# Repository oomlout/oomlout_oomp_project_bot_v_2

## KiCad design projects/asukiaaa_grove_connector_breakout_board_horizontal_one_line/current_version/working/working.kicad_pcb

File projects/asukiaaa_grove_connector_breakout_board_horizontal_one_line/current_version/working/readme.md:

# grove_connector_breakout_board
 
## summary 
* id: asukiaaa_grove_connector_breakout_board_horizontal_one_line
* user: asukiaaa
* name: grove_connector_breakout_board
* board: horizontal_one_line
* repo: https://github.com/asukiaaa/grove-connector-breakout-board
* src_file_repo_kicad_pcb: horizontal-one-line/horizontal-one-line.kicad_pcb
* src_file_repo_kicad_pcb_link: https://github.com/asukiaaa/grove-connector-breakout-board/tree/master/horizontal-one-line/horizontal-one-line.kicad_pcb
* src_file_repo_kicad_sch: horizontal-one-line/horizontal-one-line.kicad_sch
* src_file_repo_kicad_sch_link: https://github.com/asukiaaa/grove-connector-breakout-board/tree/master/horizontal-one-line/horizontal-one-line.kicad_sch

* src_file_repo_sch: 
* src_file_repo_sch_link: https://github.com/asukiaaa/grove-connector-breakout-board/tree/master/
* full details link: https://github.com/oomlout/oomlout_oomp_project_bot_v_2/tree/main/projects/asukiaaa_grove_connector_breakout_board_horizontal_one_line/current_version/working  

## schematic  
  
[schematic (pdf)](working_schematic.pdf) 

## pcb  

[board (pdf)](working.pdf)  

## working_bom
| Id | Designator | Footprint | Quantity | Designation | Supplier and ref |  | None | 
| --- | --- | --- | --- | --- | --- | --- | --- | 
| 1 | J1 | NS-Tech_Grove_1x04_P2mm_Horizontal_silk_inside | 1 | Grove-I2C-connector |  |  | [''] | 
| 2 | fid1,fid1 | Fiducial_0.5mm_Mask1mm | 2 | Fiducial_0.5mm_Mask1mm |  |  | [''] | 
| 3 | J2 | PinHeader_1x04_P2.54mm_Vertical_silk_inside | 1 | Conn_01x04 |  |  | [''] | 

## bom_schematic
| Ref | Qnty | Value | Cmp name | Footprint | Description | Vendor | DNP | 
| --- | --- | --- | --- | --- | --- | --- | --- | 
| J1 | 1 | Grove-I2C-connector | Grove-I2C-connector | my-kicad-footprints:NS-Tech_Grove_1x04_P2mm_Horizontalnside_silk_i |  |  |  | 
| J2 | 1 | Conn_01x04 | Conn_01x04 | my-kicad-footprints:PinHeader_1x04_P2.54mm_Vertical_silk_inside | Generic connector, single row, 01x04, script generated (kicad-library-utils/schlib/autogen/connector/) |  |  |

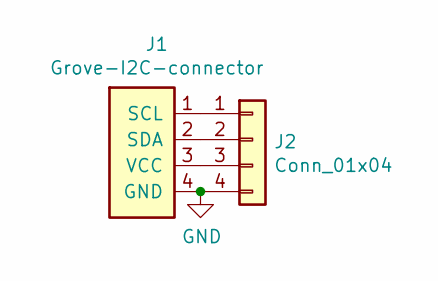
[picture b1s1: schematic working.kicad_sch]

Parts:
J1: Grove-I2C-connector; NS-Tech_Grove_1x04_P2mm_Horizontalnside_silk_i
J2: Conn_01x04; PinHeader_1x04_P2.54mm_Vertical_silk_inside

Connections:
GND: J1.4 (GND), J2.4
unnamed: J1.1 (SCL), J2.1
unnamed: J1.2 (SDA), J2.2
unnamed: J1.3 (VCC), J2.3

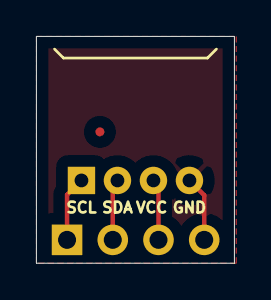
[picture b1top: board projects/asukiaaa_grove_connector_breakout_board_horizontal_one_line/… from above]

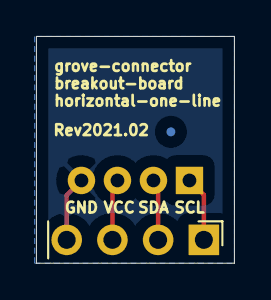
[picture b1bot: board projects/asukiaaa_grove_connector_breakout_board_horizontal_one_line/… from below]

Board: 2 copper layers, 11.0 x 12.6 mm, 4 parts (2 on the bottom side), 4 nets.

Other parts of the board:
fid1, fid1#2: Fiducial_0.5mm_Mask1mm

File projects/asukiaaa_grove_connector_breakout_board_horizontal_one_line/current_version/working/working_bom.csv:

"Id";"Designator";"Footprint";"Quantity";"Designation";"Supplier and ref";
1;"J1";"NS-Tech_Grove_1x04_P2mm_Horizontal_silk_inside";1;"Grove-I2C-connector";;;
2;"fid1,fid1";"Fiducial_0.5mm_Mask1mm";2;"Fiducial_0.5mm_Mask1mm";;;
3;"J2";"PinHeader_1x04_P2.54mm_Vertical_silk_inside";1;"Conn_01x04";;;

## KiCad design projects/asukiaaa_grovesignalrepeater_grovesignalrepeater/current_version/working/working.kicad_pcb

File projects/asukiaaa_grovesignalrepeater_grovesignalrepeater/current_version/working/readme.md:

# grovesignalrepeater
 
## summary 
* id: asukiaaa_grovesignalrepeater_grovesignalrepeater
* user: asukiaaa
* name: grovesignalrepeater
* board: grovesignalrepeater
* repo: https://github.com/asukiaaa/GroveSignalRepeater
* src_file_repo_kicad_pcb: GroveSignalRepeater.kicad_pcb
* src_file_repo_kicad_pcb_link: https://github.com/asukiaaa/GroveSignalRepeater/tree/master/GroveSignalRepeater.kicad_pcb

* src_file_repo_sch: GroveSignalRepeater.sch
* src_file_repo_sch_link: https://github.com/asukiaaa/GroveSignalRepeater/tree/master/GroveSignalRepeater.sch
* full details link: https://github.com/oomlout/oomlout_oomp_project_bot_v_2/tree/main/projects/asukiaaa_grovesignalrepeater_grovesignalrepeater/current_version/working  

## schematic  
  
[schematic (pdf)](working_schematic.pdf) 

## pcb  

[board (pdf)](working.pdf)  

## working_bom
| Id | Designator | Footprint | Quantity | Designation | Supplier and ref |  | None | 
| --- | --- | --- | --- | --- | --- | --- | --- | 
| 1 | J1,J2 | NS-Tech_Grove_1x04_P2mm_Horizontal | 2 | Conn_01x04 |  |  | [''] | 
| 2 | Q1,Q2,Q3,Q4 | SOT-23 | 4 | Q_NMOS_GSD |  |  | [''] | 
| 3 | R1,R2,R3,R4,R5,R6 | R_0603_1608Metric | 6 | 10k |  |  | [''] | 

## bom_schematic
| Ref | Qnty | Value | Cmp name | Footprint | Description | Vendor | DNP | 
| --- | --- | --- | --- | --- | --- | --- | --- | 
| J1, J2 | 2 | Conn_01x04 | Conn_01x04 | my-kicad-footprints:NS-Tech_Grove_1x04_P2mm_Horizontal | Generic connector, single row, 01x04, script generated (kicad-library-utils/schlib/autogen/connector/) |  |  | 
| Q1, Q2, Q3, Q4 | 4 | Q_NMOS_GSD | Q_NMOS_GSD | Package_TO_SOT_SMD:SOT-23 | N-MOSFET transistor, gate/source/drain |  |  | 
| R1, R2, R3, R4, R5, R6 | 6 | 10k | R | Resistor_SMD:R_0603_1608Metric | Resistor |  |  |

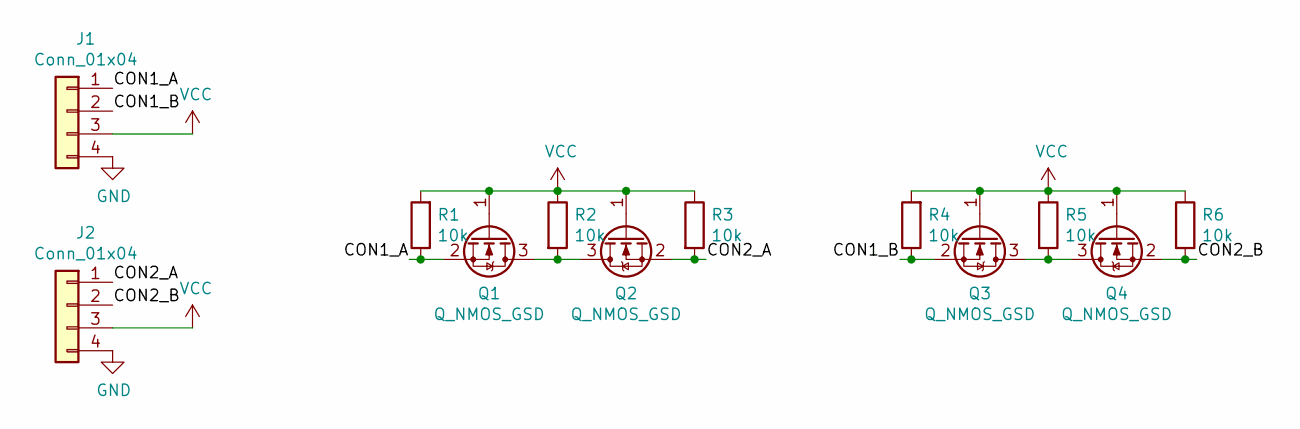
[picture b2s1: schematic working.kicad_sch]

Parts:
J1, J2: Conn_01x04; NS-Tech_Grove_1x04_P2mm_Horizontal
Q1, Q2, Q3, Q4: Q_NMOS_GSD; SOT-23
R1, R2, R3, R4, R5, R6: 10k; R_0603_1608Metric

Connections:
/CON1_A: J1.1, Q1.2 (S), R1.1
/CON1_B: J1.2, Q3.2 (S), R4.1
/CON2_A: J2.1, Q2.2 (S), R3.2
/CON2_B: J2.2, Q4.2 (S), R6.2
GND: J1.4, J2.4
unnamed: Q1.3 (D), Q2.3 (D), R2.2
unnamed: Q3.3 (D), Q4.3 (D), R5.2
VCC: J1.3, J2.3, Q1.1 (G), Q2.1 (G), Q3.1 (G), Q4.1 (G), R1.2, R2.1, R3.1, R4.2, R5.1, R6.1

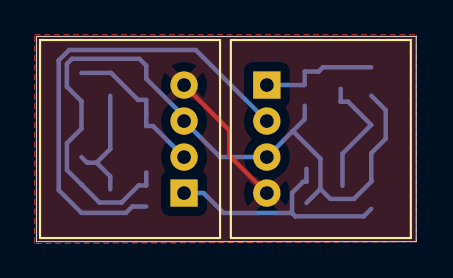
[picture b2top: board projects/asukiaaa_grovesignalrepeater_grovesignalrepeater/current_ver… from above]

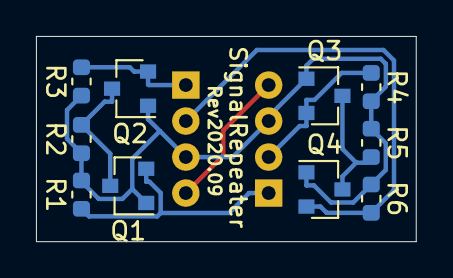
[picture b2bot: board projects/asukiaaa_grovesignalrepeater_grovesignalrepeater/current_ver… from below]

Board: 2 copper layers, 21.1 x 11.4 mm, 12 parts (10 on the bottom side), 8 nets.

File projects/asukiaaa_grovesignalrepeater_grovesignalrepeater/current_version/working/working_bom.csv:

"Id";"Designator";"Footprint";"Quantity";"Designation";"Supplier and ref";
1;"J1,J2";"NS-Tech_Grove_1x04_P2mm_Horizontal";2;"Conn_01x04";;;
2;"Q1,Q2,Q3,Q4";"SOT-23";4;"Q_NMOS_GSD";;;
3;"R1,R2,R3,R4,R5,R6";"R_0603_1608Metric";6;"10k";;;

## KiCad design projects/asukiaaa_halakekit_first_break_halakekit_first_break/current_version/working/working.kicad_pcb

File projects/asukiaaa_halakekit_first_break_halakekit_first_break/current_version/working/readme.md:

# halakekit_first_break
 
## summary 
* id: asukiaaa_halakekit_first_break_halakekit_first_break
* user: asukiaaa
* name: halakekit_first_break
* board: halakekit_first_break
* repo: https://github.com/asukiaaa/halakekit_first_break
* src_file_repo_kicad_pcb: halakekit_first_break.kicad_pcb
* src_file_repo_kicad_pcb_link: https://github.com/asukiaaa/halakekit_first_break/tree/master/halakekit_first_break.kicad_pcb

* src_file_repo_sch: halakekit_first_break.sch
* src_file_repo_sch_link: https://github.com/asukiaaa/halakekit_first_break/tree/master/halakekit_first_break.sch
* full details link: https://github.com/oomlout/oomlout_oomp_project_bot_v_2/tree/main/projects/asukiaaa_halakekit_first_break_halakekit_first_break/current_version/working  

## schematic  
  
[schematic (pdf)](working_schematic.pdf) 

## pcb  

[board (pdf)](working.pdf)  

## working_bom
| Id | Designator | Footprint | Quantity | Designation | Supplier and ref |  | None | 
| --- | --- | --- | --- | --- | --- | --- | --- | 
| 1 | J21,J22 | Pin_Header_Straight_1x10 | 2 | LINE_10 |  |  | [''] | 
| 2 | J26 | Pin_Header_Straight_1x02 | 1 | HEADER_2 |  |  | [''] | 
| 3 | J27 | Pin_Header_Straight_1x12 | 1 | HEADER_12 |  |  | [''] | 
| 4 | U1 | Arduino Pro Micro | 1 | Arduino_Pro_Micro |  |  | [''] | 
| 5 | G***,G***,G*** | nyampass_logo_8p4mm | 3 | LOGO |  |  | [''] | 
| 6 | J1,J2,J3,J4,J5,J11,J12,J13,J14,J15 | Pin_Header_Connect_1x04 | 10 | LINE_4 |  |  | [''] | 
| 7 | J6 | Pin_Header_Straight_1x10 | 1 | HEADER_10 |  |  | [''] | 
| 8 | J9,J10,J7,J8 | Pin_Header_Straight_1x04 | 4 | Connector_4 |  |  | [''] | 
| 9 | J24,J28 | Pin_Header_Circle_1x04 | 2 | CIRCLES_4 |  |  | [''] | 

## bom_schematic
| Ref | Qnty | Value | Cmp name | Footprint | Description | Vendor | DNP | 
| --- | --- | --- | --- | --- | --- | --- | --- | 
| J1, J2, J3, J4, J5, J11, J12, J13, J14, J15 | 10 | LINE_4 | HEADER_4 | simple_headers:Pin_Header_Connect_1x04 |  |  |  | 
| J6 | 1 | HEADER_10 | HEADER_10 | simple_headers:Pin_Header_Straight_1x10 |  |  |  | 
| J7, J8, J9, J10 | 4 | Connector_4 | HEADER_4 | simple_headers:Pin_Header_Straight_1x04 |  |  |  | 
| J21, J22 | 2 | LINE_10 | HEADER_10 | simple_headers:Pin_Header_Straight_1x10 |  |  |  | 
| J24, J28 | 2 | CIRCLES_4 | HEADER_4 | simple_headers:Pin_Header_Circle_1x04 |  |  |  | 
| J26 | 1 | HEADER_2 | HEADER_2 | simple_headers:Pin_Header_Straight_1x02 |  |  |  | 
| J27 | 1 | HEADER_12 | HEADER_12 | simple_headers:Pin_Header_Straight_1x12 |  |  |  | 
| U1 | 1 | Arduino_Pro_Micro | Arduino_Pro_Micro | arduino_pro_micro:Arduino Pro Micro |  |  |  |

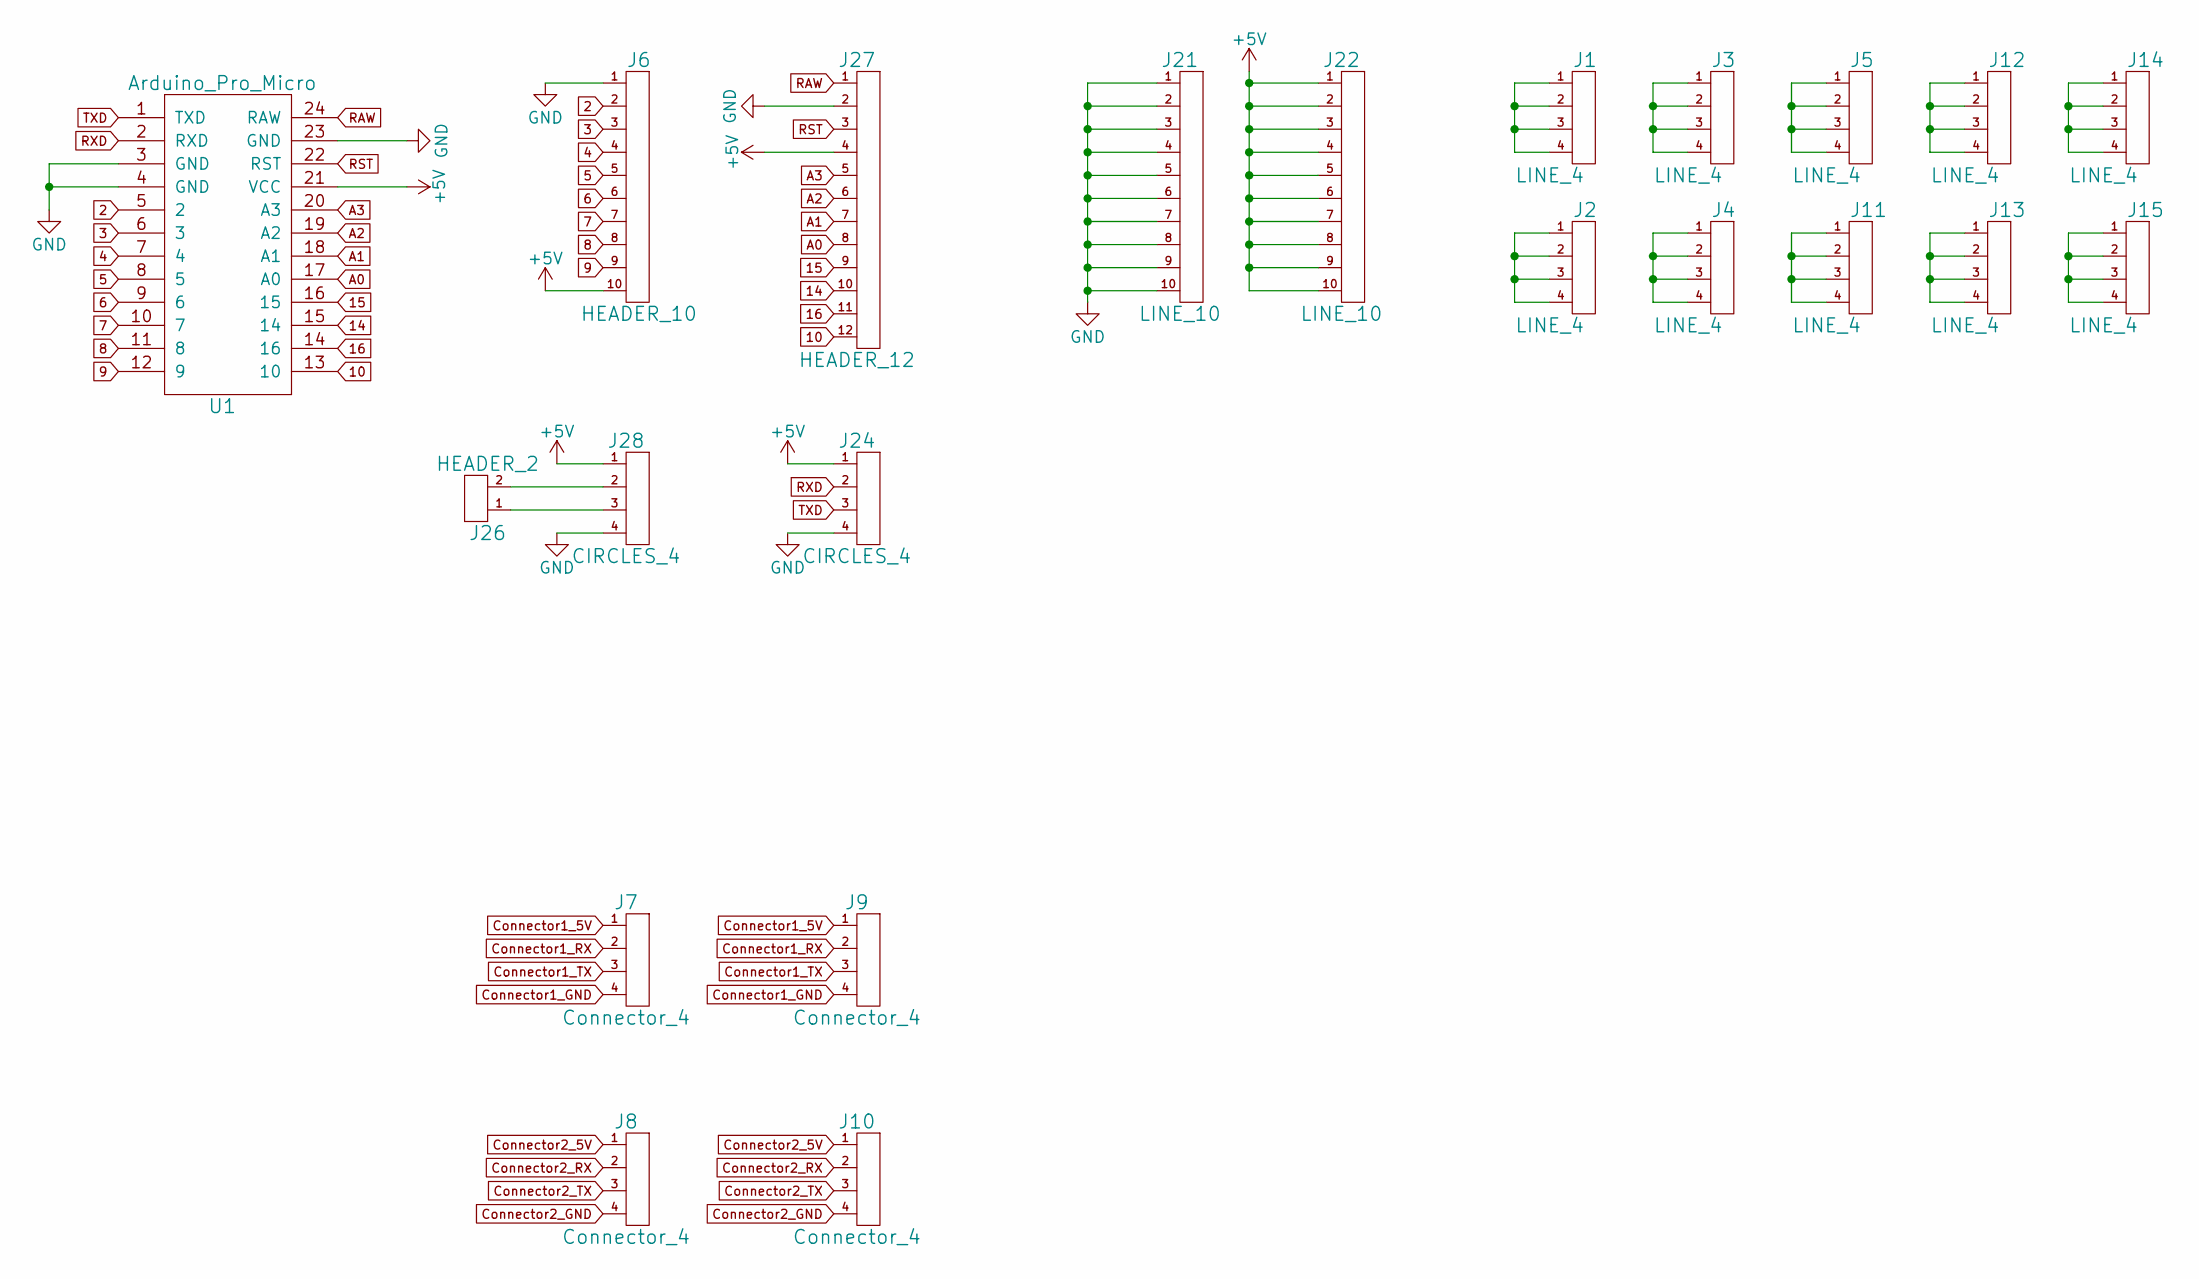
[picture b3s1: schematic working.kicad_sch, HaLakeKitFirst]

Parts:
J1, J2, J3, J4, J5, J11, J12, J13, J14, J15: LINE_4; Pin_Header_Connect_1x04
J6: HEADER_10; Pin_Header_Straight_1x10
J7, J8, J9, J10: Connector_4; Pin_Header_Straight_1x04
J21, J22: LINE_10; Pin_Header_Straight_1x10
J24, J28: CIRCLES_4; Pin_Header_Circle_1x04
J26: HEADER_2; Pin_Header_Straight_1x02
J27: HEADER_12; Pin_Header_Straight_1x12
U1: Arduino_Pro_Micro; Arduino Pro Micro

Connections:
2: J6.2, U1.5 (2)
3: J6.3, U1.6 (3)
4: J6.4, U1.7 (4)
5: J6.5, U1.8 (5)
6: J6.6, U1.9 (6)
7: J6.7, U1.10 (7)
8: J6.8, U1.11 (8)
9: J6.9, U1.12 (9)
10: J27.12, U1.13 (10)
14: J27.10, U1.15 (14)
15: J27.9, U1.16 (15)
16: J27.11, U1.14 (16)
+5V: J6.10, J22.1, J22.2, J22.3, J22.4, J22.5, J22.6, J22.7, J22.8, J22.9, J22.10, J24.1, J27.4, J28.1, U1.21 (VCC)
A0: J27.8, U1.17 (A0)
A1: J27.7, U1.18 (A1)
A2: J27.6, U1.19 (A2)
A3: J27.5, U1.20 (A3)
Connector1_5V: J7.1, J9.1
Connector1_GND: J7.4, J9.4
Connector1_RX: J7.2, J9.2
Connector1_TX: J7.3, J9.3
Connector2_5V: J8.1, J10.1
Connector2_GND: J8.4, J10.4
Connector2_RX: J8.2, J10.2
Connector2_TX: J8.3, J10.3
GND: J6.1, J21.1, J21.2, J21.3, J21.4, J21.5, J21.6, J21.7, J21.8, J21.9, J21.10, J24.4, J27.2, J28.4, U1.3 (GND), U1.4 (GND), U1.23 (GND)
unnamed: J1.1, J1.2, J1.3, J1.4
unnamed: J2.1, J2.2, J2.3, J2.4
unnamed: J3.1, J3.2, J3.3, J3.4
unnamed: J4.1, J4.2, J4.3, J4.4
unnamed: J5.1, J5.2, J5.3, J5.4
unnamed: J11.1, J11.2, J11.3, J11.4
unnamed: J12.1, J12.2, J12.3, J12.4
unnamed: J13.1, J13.2, J13.3, J13.4
unnamed: J14.1, J14.2, J14.3, J14.4
unnamed: J15.1, J15.2, J15.3, J15.4
unnamed: J26.1, J28.3
unnamed: J26.2, J28.2
RAW: J27.1, U1.24 (RAW)
RST: J27.3, U1.22 (RST)
RXD: J24.2, U1.2 (RXD)
TXD: J24.3, U1.1 (TXD)

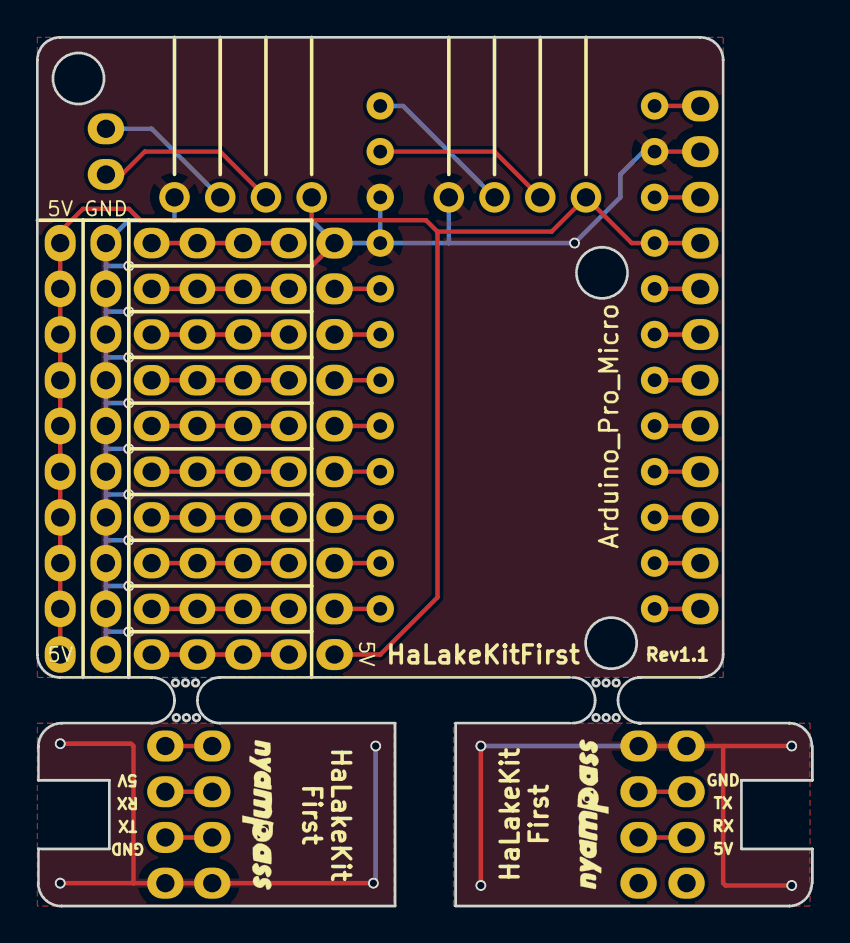
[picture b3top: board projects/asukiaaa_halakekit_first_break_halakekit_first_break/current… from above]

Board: 2 copper layers, 43.1 x 48.3 mm, 22 parts (0 on the bottom side), 42 nets.

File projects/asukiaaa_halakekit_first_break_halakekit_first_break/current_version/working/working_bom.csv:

"Id";"Designator";"Footprint";"Quantity";"Designation";"Supplier and ref";
1;"J21,J22";"Pin_Header_Straight_1x10";2;"LINE_10";;;
2;"J26";"Pin_Header_Straight_1x02";1;"HEADER_2";;;
3;"J27";"Pin_Header_Straight_1x12";1;"HEADER_12";;;
4;"U1";"Arduino Pro Micro";1;"Arduino_Pro_Micro";;;
5;"G***,G***,G***";"nyampass_logo_8p4mm";3;"LOGO";;;
6;"J1,J2,J3,J4,J5,J11,J12,J13,J14,J15";"Pin_Header_Connect_1x04";10;"LINE_4";;;
7;"J6";"Pin_Header_Straight_1x10";1;"HEADER_10";;;
8;"J9,J10,J7,J8";"Pin_Header_Straight_1x04";4;"Connector_4";;;
9;"J24,J28";"Pin_Header_Circle_1x04";2;"CIRCLES_4";;;

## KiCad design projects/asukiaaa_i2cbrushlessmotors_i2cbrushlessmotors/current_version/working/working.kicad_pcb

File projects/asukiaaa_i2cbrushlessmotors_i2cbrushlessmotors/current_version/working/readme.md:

# i2cbrushlessmotors
 
## summary 
* id: asukiaaa_i2cbrushlessmotors_i2cbrushlessmotors
* user: asukiaaa
* name: i2cbrushlessmotors
* board: i2cbrushlessmotors
* repo: https://github.com/asukiaaa/I2cBrushlessMotors
* src_file_repo_kicad_pcb: pcb/I2cBrushlessMotors.kicad_pcb
* src_file_repo_kicad_pcb_link: https://github.com/asukiaaa/I2cBrushlessMotors/tree/master/pcb/I2cBrushlessMotors.kicad_pcb

* src_file_repo_sch: pcb/I2cBrushlessMotors.sch
* src_file_repo_sch_link: https://github.com/asukiaaa/I2cBrushlessMotors/tree/master/pcb/I2cBrushlessMotors.sch
* full details link: https://github.com/oomlout/oomlout_oomp_project_bot_v_2/tree/main/projects/asukiaaa_i2cbrushlessmotors_i2cbrushlessmotors/current_version/working  

## schematic  
  
[schematic (pdf)](working_schematic.pdf) 

## pcb  

[board (pdf)](working.pdf)  

## working_bom
| Id | Designator | Footprint | Quantity | Designation | Supplier and ref |  | None | 
| --- | --- | --- | --- | --- | --- | --- | --- | 
| 1 | J3 | PinHeader_2x15_P2.54mm_M5Stack | 1 | Header |  |  | [''] | 
| 2 | J4 | PinSocket_2x15_P2.54mm_Vertical_SMD_just_for_M5Stack_bottom | 1 | Socket |  |  | [''] | 
| 3 | C1,C3 | C_0603_1608Metric | 2 | 0.1uf |  |  | [''] | 
| 4 | J2 | 2x03_P2.54mm_Pads | 1 | Conn_01x06 |  |  | [''] | 
| 5 | R3,R2,R1,R5,R8,R4,R7,R6,R9,R11,R14,R17,R10,R13,R16,R12,R15,R18 | R_0603_1608Metric | 18 | 10k |  |  | [''] | 
| 6 | J1,J5 | Molex_1x03_P1.25mm_Vertical | 2 | Conn_01x03 |  |  | [''] | 
| 7 | Q1,Q4,Q7,Q10,Q13,Q16 | SOT-23 | 6 | Q_PMOS_GSD |  |  | [''] | 
| 8 | Q2,Q3,Q5,Q8,Q6,Q9,Q11,Q14,Q17,Q12,Q15,Q18 | SOT-23 | 12 | Q_NMOS_GSD |  |  | [''] | 
| 9 | U1 | QFN-32-1EP_5x5mm_P0.5mm_EP3.1x3.1mm | 1 | ATmega328PB-MU |  |  | [''] | 
| 10 | C2 | C_0603_1608Metric | 1 | 1uf |  |  | [''] | 
| 11 | D1,D2 | D_SOD-323 | 2 | D |  |  | [''] | 
| 12 | D3 | D_SOD-123F | 1 | D |  |  | [''] | 

## bom_schematic
| Ref | Qnty | Value | Cmp name | Footprint | Description | Vendor | DNP | 
| --- | --- | --- | --- | --- | --- | --- | --- | 
| A0, A1, A4, A6 | 4 | NC | Jumper_NC_Small-Device | Jumper:SolderJumper-2_P1.3mm_Bridged_RoundedPad1.0x1.5mm |  |  |  | 
| A2, A3, A5, A7 | 4 | NO | Jumper_NO_Small-Device | Jumper:SolderJumper-2_P1.3mm_Open_RoundedPad1.0x1.5mm |  |  |  | 
| C1, C3 | 2 | 0.1uf | C | Capacitor_SMD:C_0603_1608Metric | Unpolarized capacitor |  |  | 
| C2 | 1 | 1uf | C | Capacitor_SMD:C_0603_1608Metric | Unpolarized capacitor |  |  | 
| D1, D2 | 2 | D | D | Diode_SMD:D_SOD-323 | Diode |  |  | 
| D3 | 1 | D | D | Diode_SMD:D_SOD-123F | Diode |  |  | 
| J1, J5 | 2 | Conn_01x03 | Conn_01x03 | footprints:Molex_1x03_P1.25mm_Vertical | Generic connector, single row, 01x03, script generated (kicad-library-utils/schlib/autogen/connector/) |  |  | 
| J2 | 1 | Conn_01x06 | Conn_01x06 | footprints:2x03_P2.54mm_Pads | Generic connector, single row, 01x06, script generated (kicad-library-utils/schlib/autogen/connector/) |  |  | 
| J3 | 1 | Header | Conn_02x15_Odd_Even | footprints:PinHeader_2x15_P2.54mm_M5Stack | Generic connector, double row, 02x15, odd/even pin numbering scheme (row 1 odd numbers, row 2 even numbers), script generated (kicad-library-utils/schlib/autogen/connector/) |  |  | 
| J4 | 1 | Socket | Conn_02x15_Odd_Even | footprints:PinSocket_2x15_P2.54mm_Vertical_SMD_just_for_M5Stack_bottom | Generic connector, double row, 02x15, odd/even pin numbering scheme (row 1 odd numbers, row 2 even numbers), script generated (kicad-library-utils/schlib/autogen/connector/) |  |  | 
| Q1, Q4, Q7, Q10, Q13, Q16 | 6 | Q_PMOS_GSD | Q_PMOS_GSD | Package_TO_SOT_SMD:SOT-23 | P-MOSFET transistor, gate/source/drain |  |  | 
| Q2, Q3, Q5, Q6, Q8, Q9, Q11, Q12, Q14, Q15, Q17, Q18 | 12 | Q_NMOS_GSD | Q_NMOS_GSD | Package_TO_SOT_SMD:SOT-23 | N-MOSFET transistor, gate/source/drain |  |  | 
| R1, R2, R3, R4, R5, R6, R7, R8, R9, R10, R11, R12, R13, R14, R15, R16, R17, R18 | 18 | 10k | R | Resistor_SMD:R_0603_1608Metric | Resistor |  |  | 
| U1 | 1 | ATmega328PB-MU | ATmega328PB-MU-MCU_Microchip_ATmega | Package_DFN_QFN:QFN-32-1EP_5x5mm_P0.5mm_EP3.1x3.1mm |  |  |  |

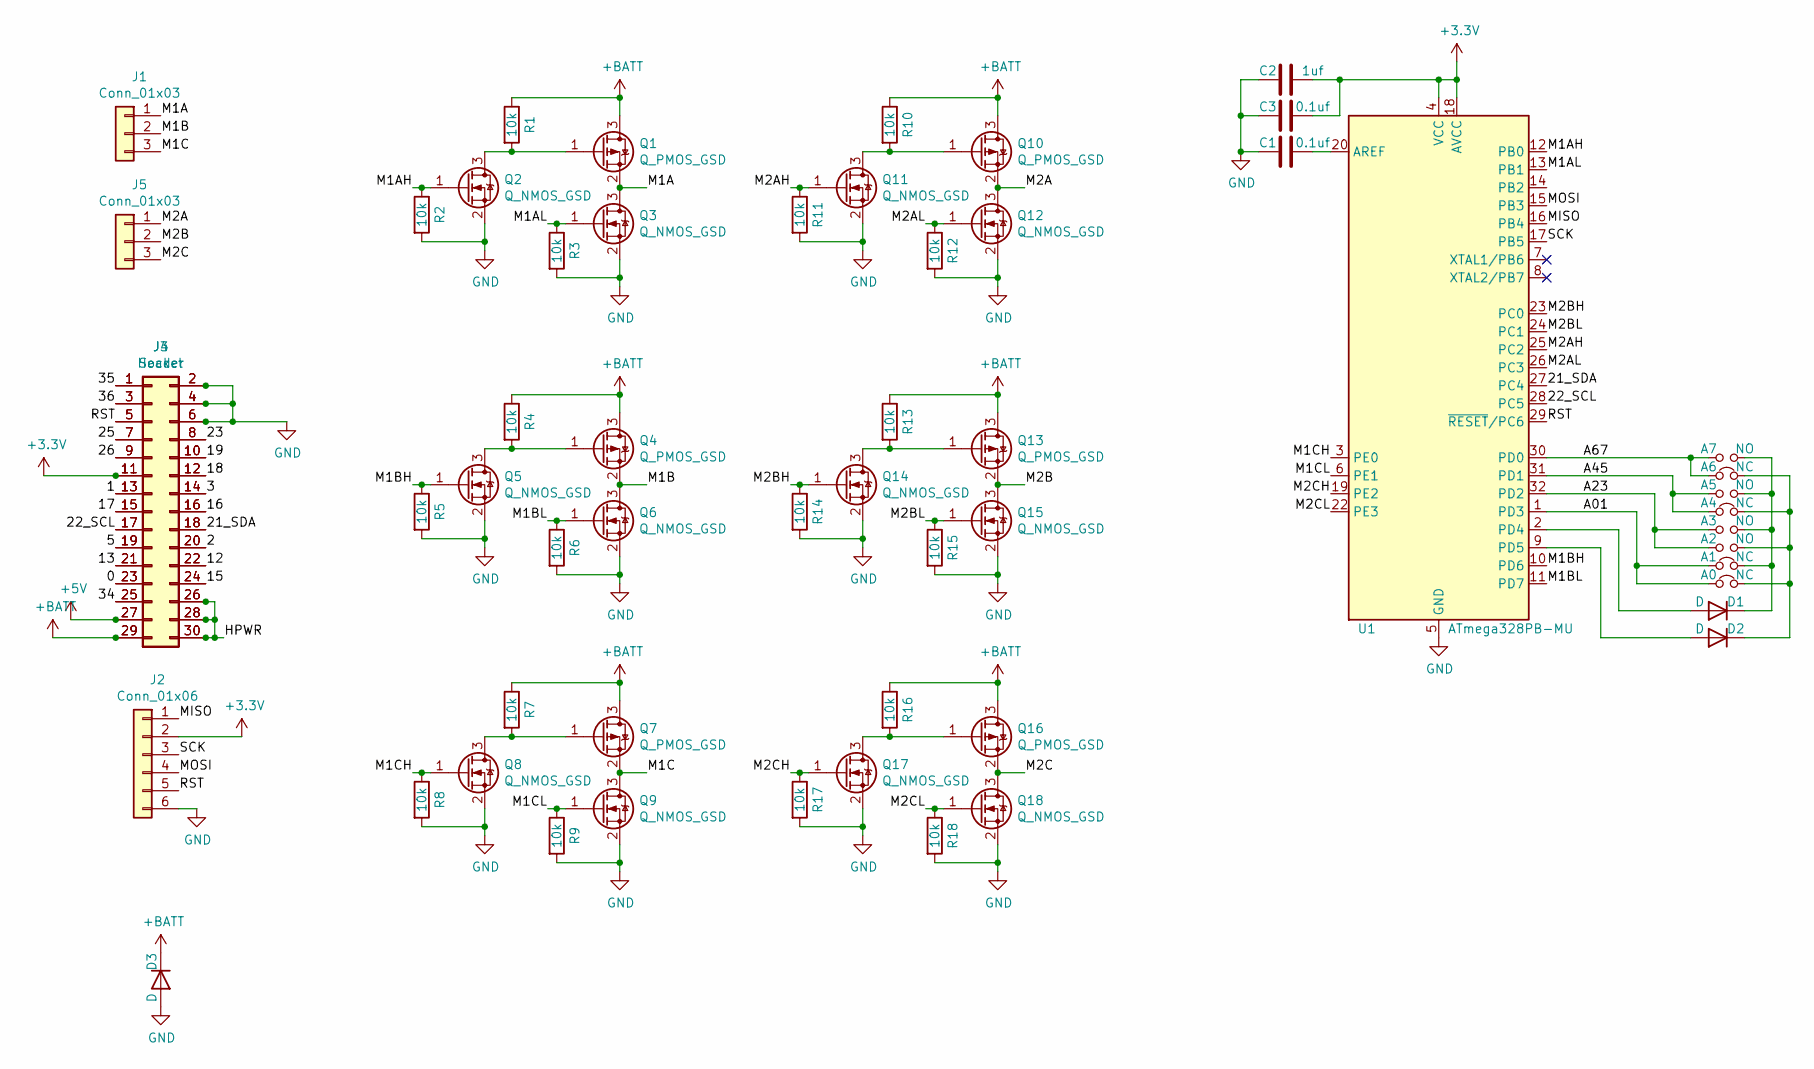
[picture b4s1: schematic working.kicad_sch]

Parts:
A0, A1, A4, A6: NC; SolderJumper-2_P1.3mm_Bridged_RoundedPad1.0x1.5mm
A2, A3, A5, A7: NO; SolderJumper-2_P1.3mm_Open_RoundedPad1.0x1.5mm
C1, C3: 0.1uf; C_0603_1608Metric
C2: 1uf; C_0603_1608Metric
D1, D2: D; D_SOD-323
D3: D; D_SOD-123F
J1, J5: Conn_01x03; Molex_1x03_P1.25mm_Vertical
J2: Conn_01x06; 2x03_P2.54mm_Pads
J3: Header; PinHeader_2x15_P2.54mm_M5Stack
J4: Socket; PinSocket_2x15_P2.54mm_Vertical_SMD_just_for_M5Stack_bottom
Q1, Q4, Q7, Q10, Q13, Q16: Q_PMOS_GSD; SOT-23
Q2, Q3, Q5, Q6, Q8, Q9, Q11, Q12, Q14, Q15, Q17, Q18: Q_NMOS_GSD; SOT-23
R1, R2, R3, R4, R5, R6, R7, R8, R9, R10, R11, R12, R13, R14, R15, R16, R17, R18: 10k; R_0603_1608Metric
U1: ATmega328PB-MU; QFN-32-1EP_5x5mm_P0.5mm_EP3.1x3.1mm

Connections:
+3V3: C2.2, C3.2, J2.2, J3.11, J4.11, U1.4 (VCC), U1.18 (AVCC)
+5V: J3.27, J4.27
+BATT: D3.1 (K), J3.29, J4.29, Q1.3 (D), Q4.3 (D), Q7.3 (D), Q10.3 (D), Q13.3 (D), Q16.3 (D), R1.1, R4.1, R7.1, R10.1, R13.1, R16.1
/0: J3.23, J4.23
/1: J3.13, J4.13
/2: J3.20, J4.20
/3: J3.14, J4.14
/5: J3.19, J4.19
/12: J3.22, J4.22
/13: J3.21, J4.21
/15: J3.24, J4.24
/16: J3.16, J4.16
/17: J3.15, J4.15
/18: J3.12, J4.12
/19: J3.10, J4.10
/21_SDA: J3.18, J4.18, U1.27 (PC4)
/22_SCL: J3.17, J4.17, U1.28 (PC5)
/23: J3.8, J4.8
/25: J3.7, J4.7
/26: J3.9, J4.9
/34: J3.25, J4.25
/35: J3.1, J4.1
/36: J3.3, J4.3
/A01: A0.1, A1.1, U1.1 (PD3)
/A23: A2.1, A3.1, U1.32 (PD2)
/A45: A4.1, A5.1, U1.31 (PD1)
/A67: A6.1, A7.1, U1.30 (PD0)
/HPWR: J3.26, J3.28, J3.30, J4.26, J4.28, J4.30
/M1A: J1.1, Q1.2 (S), Q3.3 (D)
/M1AH: Q2.1 (G), R2.1, U1.12 (PB0)
/M1AL: Q3.1 (G), R3.1, U1.13 (PB1)
/M1B: J1.2, Q4.2 (S), Q6.3 (D)
/M1BH: Q5.1 (G), R5.1, U1.10 (PD6)
/M1BL: Q6.1 (G), R6.1, U1.11 (PD7)
/M1C: J1.3, Q7.2 (S), Q9.3 (D)
/M1CH: Q8.1 (G), R8.1, U1.3 (PE0)
/M1CL: Q9.1 (G), R9.1, U1.6 (PE1)
/M2A: J5.1, Q10.2 (S), Q12.3 (D)
/M2AH: Q11.1 (G), R11.1, U1.25 (PC2)
/M2AL: Q12.1 (G), R12.1, U1.26 (PC3)
/M2B: J5.2, Q13.2 (S), Q15.3 (D)
/M2BH: Q14.1 (G), R14.1, U1.23 (PC0)
/M2BL: Q15.1 (G), R15.1, U1.24 (PC1)
/M2C: J5.3, Q16.2 (S), Q18.3 (D)
/M2CH: Q17.1 (G), R17.1, U1.19 (PE2)
/M2CL: Q18.1 (G), R18.1, U1.22 (PE3)
/MISO: J2.1, U1.16 (PB4)
/MOSI: J2.4, U1.15 (PB3)
/RST: J2.5, J3.5, J4.5, U1.29 (~RESET/PC6)
/SCK: J2.3, U1.17 (PB5)
GND: C1.1, C2.1, C3.1, D3.2 (A), J2.6, J3.2, J3.4, J3.6, J4.2, J4.4, J4.6, Q2.2 (S), Q3.2 (S), Q5.2 (S), Q6.2 (S), Q8.2 (S), Q9.2 (S), Q11.2 (S), Q12.2 (S), Q14.2 (S), Q15.2 (S), Q17.2 (S), Q18.2 (S), R2.2, R3.2, R5.2, R6.2, R8.2, R9.2, R11.2, R12.2, R14.2, R15.2, R17.2, R18.2, U1.5 (GND), U1.21 (GND), U1.33 (GND)
unnamed: A0.2, A2.2, A4.2, A6.2, D2.1 (K)
unnamed: A1.2, A3.2, A5.2, A7.2, D1.1 (K)
unnamed: C1.2, U1.20 (AREF)
unnamed: D1.2 (A), U1.2 (PD4)
unnamed: D2.2 (A), U1.9 (PD5)
unnamed: Q1.1 (G), Q2.3 (D), R1.2
unnamed: Q4.1 (G), Q5.3 (D), R4.2
unnamed: Q7.1 (G), Q8.3 (D), R7.2
unnamed: Q10.1 (G), Q11.3 (D), R10.2
unnamed: Q13.1 (G), Q14.3 (D), R13.2
unnamed: Q16.1 (G), Q17.3 (D), R16.2

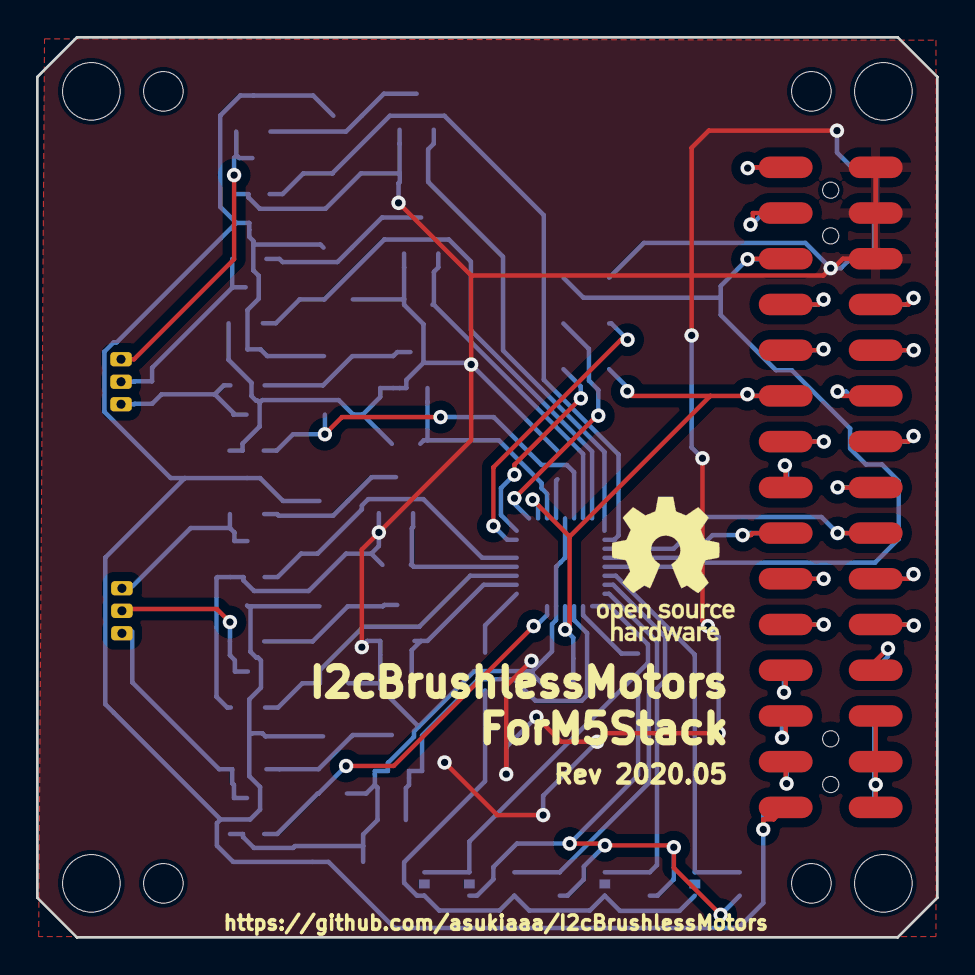
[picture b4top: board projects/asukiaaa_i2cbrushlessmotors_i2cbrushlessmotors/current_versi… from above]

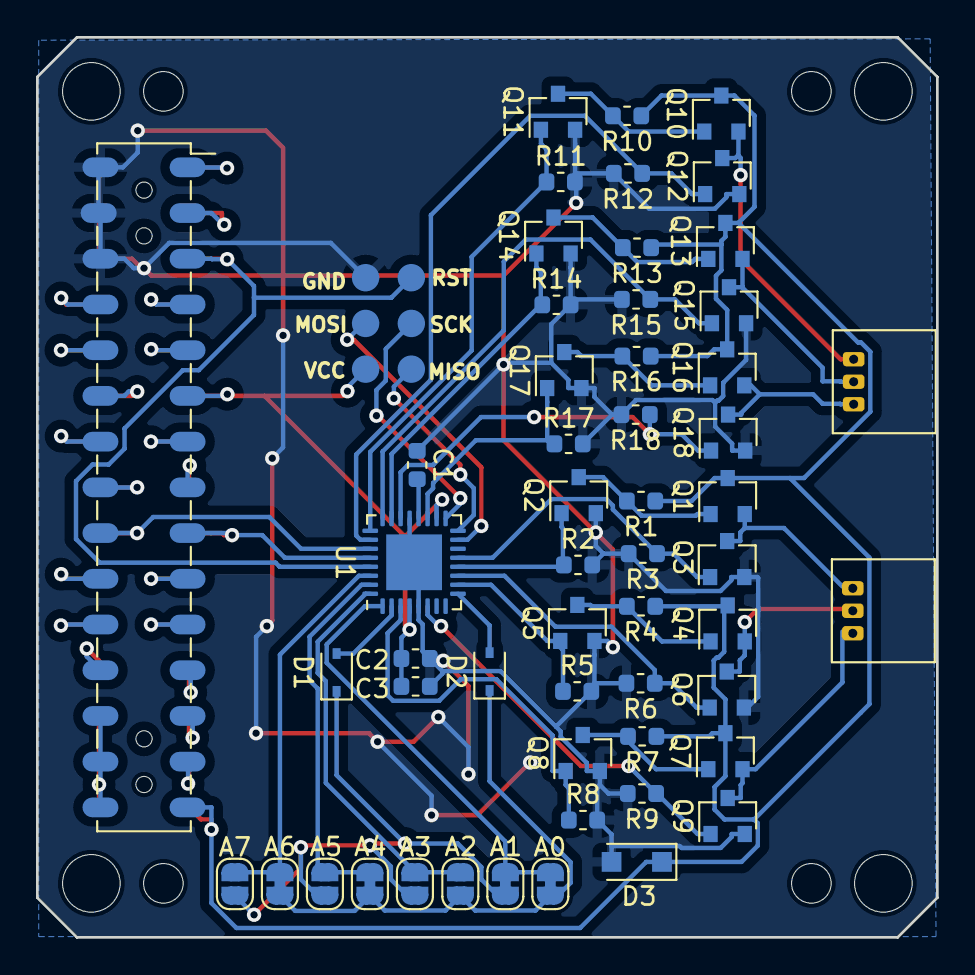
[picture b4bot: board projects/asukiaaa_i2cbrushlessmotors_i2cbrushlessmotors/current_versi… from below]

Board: 2 copper layers, 50.0 x 50.0 mm, 64 parts (55 on the bottom side), 62 nets.

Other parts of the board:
REF1, REF4, REF6, REF9: MountingHole_3.2mm_M3
REF2, REF3, REF7, REF8: MountingHole_2.2mm_M2

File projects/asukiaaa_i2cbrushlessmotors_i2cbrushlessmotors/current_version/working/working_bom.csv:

"Id";"Designator";"Footprint";"Quantity";"Designation";"Supplier and ref";
1;"J3";"PinHeader_2x15_P2.54mm_M5Stack";1;"Header";;;
2;"J4";"PinSocket_2x15_P2.54mm_Vertical_SMD_just_for_M5Stack_bottom";1;"Socket";;;
3;"C1,C3";"C_0603_1608Metric";2;"0.1uf";;;
4;"J2";"2x03_P2.54mm_Pads";1;"Conn_01x06";;;
5;"R3,R2,R1,R5,R8,R4,R7,R6,R9,R11,R14,R17,R10,R13,R16,R12,R15,R18";"R_0603_1608Metric";18;"10k";;;
6;"J1,J5";"Molex_1x03_P1.25mm_Vertical";2;"Conn_01x03";;;
7;"Q1,Q4,Q7,Q10,Q13,Q16";"SOT-23";6;"Q_PMOS_GSD";;;
8;"Q2,Q3,Q5,Q8,Q6,Q9,Q11,Q14,Q17,Q12,Q15,Q18";"SOT-23";12;"Q_NMOS_GSD";;;
9;"U1";"QFN-32-1EP_5x5mm_P0.5mm_EP3.1x3.1mm";1;"ATmega328PB-MU";;;
10;"C2";"C_0603_1608Metric";1;"1uf";;;
11;"D1,D2";"D_SOD-323";2;"D";;;
12;"D3";"D_SOD-123F";1;"D";;;

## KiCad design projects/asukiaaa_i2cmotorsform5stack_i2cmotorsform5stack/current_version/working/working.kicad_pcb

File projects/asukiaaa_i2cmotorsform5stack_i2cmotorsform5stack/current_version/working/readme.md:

# i2cmotorsform5stack
 
## summary 
* id: asukiaaa_i2cmotorsform5stack_i2cmotorsform5stack
* user: asukiaaa
* name: i2cmotorsform5stack
* board: i2cmotorsform5stack
* repo: https://github.com/asukiaaa/I2cMotorsForM5Stack
* src_file_repo_kicad_pcb: pcb/I2cMotorsForM5Stack.kicad_pcb
* src_file_repo_kicad_pcb_link: https://github.com/asukiaaa/I2cMotorsForM5Stack/tree/master/pcb/I2cMotorsForM5Stack.kicad_pcb

* src_file_repo_sch: pcb/I2cMotorsForM5Stack.sch
* src_file_repo_sch_link: https://github.com/asukiaaa/I2cMotorsForM5Stack/tree/master/pcb/I2cMotorsForM5Stack.sch
* full details link: https://github.com/oomlout/oomlout_oomp_project_bot_v_2/tree/main/projects/asukiaaa_i2cmotorsform5stack_i2cmotorsform5stack/current_version/working  

## schematic  
  
[schematic (pdf)](working_schematic.pdf) 

## pcb  

[board (pdf)](working.pdf)  

## working_bom
| Id | Designator | Footprint | Quantity | Designation | Supplier and ref |  | None | 
| --- | --- | --- | --- | --- | --- | --- | --- | 
| 1 | J1 | Hirose_FH12-30S-0.5SH_1x30-1MP_P0.50mm_Horizontal | 1 | FFC_connector |  |  | [''] | 
| 2 | C1,C2,C4 | C_0603_1608Metric | 3 | 0.1uf |  |  | [''] | 
| 3 | U1 | SSOP-24_5.3x8.2mm_P0.65mm | 1 | TB6612FNG |  |  | [''] | 
| 4 | C3 | C_0805_2012Metric | 1 | 10uf |  |  | [''] | 
| 5 | J3 | 2x03_P2.54mm_Pads | 1 | Conn_01x06 |  |  | [''] | 
| 6 | D1,D2,D3 | D_SOD-123F | 3 | D |  |  | [''] | 
| 7 | J4 | TerminalBlock_bornier-6_P5.08mm | 1 | Conn_01x06 |  |  | [''] | 
| 8 | U2 | QFN-32-1EP_5x5mm_P0.5mm_EP3.1x3.1mm | 1 | ATmega328PB-MU |  |  | [''] | 
| 9 | J5 | NS-Tech_Grove_1x04_P2mm_Vertical | 1 | Conn_01x04 |  |  | [''] | 
| 10 | J2 | PinSocket_2x15_P2.54mm_Vertical_SMD_just_for_M5Stack_bottom | 1 | 2x15socket |  |  | [''] | 

## bom_schematic
| Ref | Qnty | Value | Cmp name | Footprint | Description | Vendor | DNP | 
| --- | --- | --- | --- | --- | --- | --- | --- | 
| ADDR0, ADDR2, ADDR3, ADDR5, ADDR7 | 5 | NO | Jumper_NO_Small-Device-I2cMotorsForM5Stack-rescue | Jumper:SolderJumper-2_P1.3mm_Open_RoundedPad1.0x1.5mm |  |  |  | 
| ADDR1, ADDR4, ADDR6 | 3 | NC | Jumper_NC_Small-Device-I2cMotorsForM5Stack-rescue | Jumper:SolderJumper-2_P1.3mm_Bridged_RoundedPad1.0x1.5mm |  |  |  | 
| C1, C2, C4 | 3 | 0.1uf | C | Capacitor_SMD:C_0603_1608Metric | Unpolarized capacitor |  |  | 
| C3 | 1 | 10uf | C | Capacitor_SMD:C_0805_2012Metric | Unpolarized capacitor |  |  | 
| D1, D2, D3 | 3 | D | D | Diode_SMD:D_SOD-123F | Diode |  |  | 
| J1 | 1 | FFC_connector | Conn_02x15_Odd_Even | Connector_FFC-FPC:Hirose_FH12-30S-0.5SH_1x30-1MP_P0.50mm_Horizontal | Generic connector, double row, 02x15, odd/even pin numbering scheme (row 1 odd numbers, row 2 even numbers), script generated (kicad-library-utils/schlib/autogen/connector/) |  |  | 
| J2 | 1 | 2x15socket | Conn_02x15_Odd_Even | my-kicad-footprints:PinSocket_2x15_P2.54mm_Vertical_SMD_just_for_M5Stack_bottom | Generic connector, double row, 02x15, odd/even pin numbering scheme (row 1 odd numbers, row 2 even numbers), script generated (kicad-library-utils/schlib/autogen/connector/) |  |  | 
| J3 | 1 | Conn_01x06 | Conn_01x06 | footprints:2x03_P2.54mm_Pads | Generic connector, single row, 01x06, script generated (kicad-library-utils/schlib/autogen/connector/) |  |  | 
| J4 | 1 | Conn_01x06 | Conn_01x06 | TerminalBlock:TerminalBlock_bornier-6_P5.08mm | Generic connector, single row, 01x06, script generated (kicad-library-utils/schlib/autogen/connector/) |  |  | 
| J5 | 1 | Conn_01x04 | Conn_01x04 | Connector:NS-Tech_Grove_1x04_P2mm_Vertical | Generic connector, single row, 01x04, script generated (kicad-library-utils/schlib/autogen/connector/) |  |  | 
| JP1 | 1 | NC | Jumper_NC_Small-Device-I2cMotorsForM5Stack-rescue | Jumper:SolderJumper-2_P1.3mm_Bridged_RoundedPad1.0x1.5mm |  |  |  | 
| JP2 | 1 | NO | Jumper_NO_Small-Device-I2cMotorsForM5Stack-rescue | Jumper:SolderJumper-2_P1.3mm_Open_RoundedPad1.0x1.5mm |  |  |  | 
| U1 | 1 | TB6612FNG | TB6612FNG-Driver_Motor-I2cMotorsForM5Stack-rescue | Package_SO:SSOP-24_5.3x8.2mm_P0.65mm |  |  |  | 
| U2 | 1 | ATmega328PB-MU | ATmega328PB-MU-MCU_Microchip_ATmega-I2cMotorsForM5Stack-rescue | Package_DFN_QFN:QFN-32-1EP_5x5mm_P0.5mm_EP3.1x3.1mm |  |  |  |

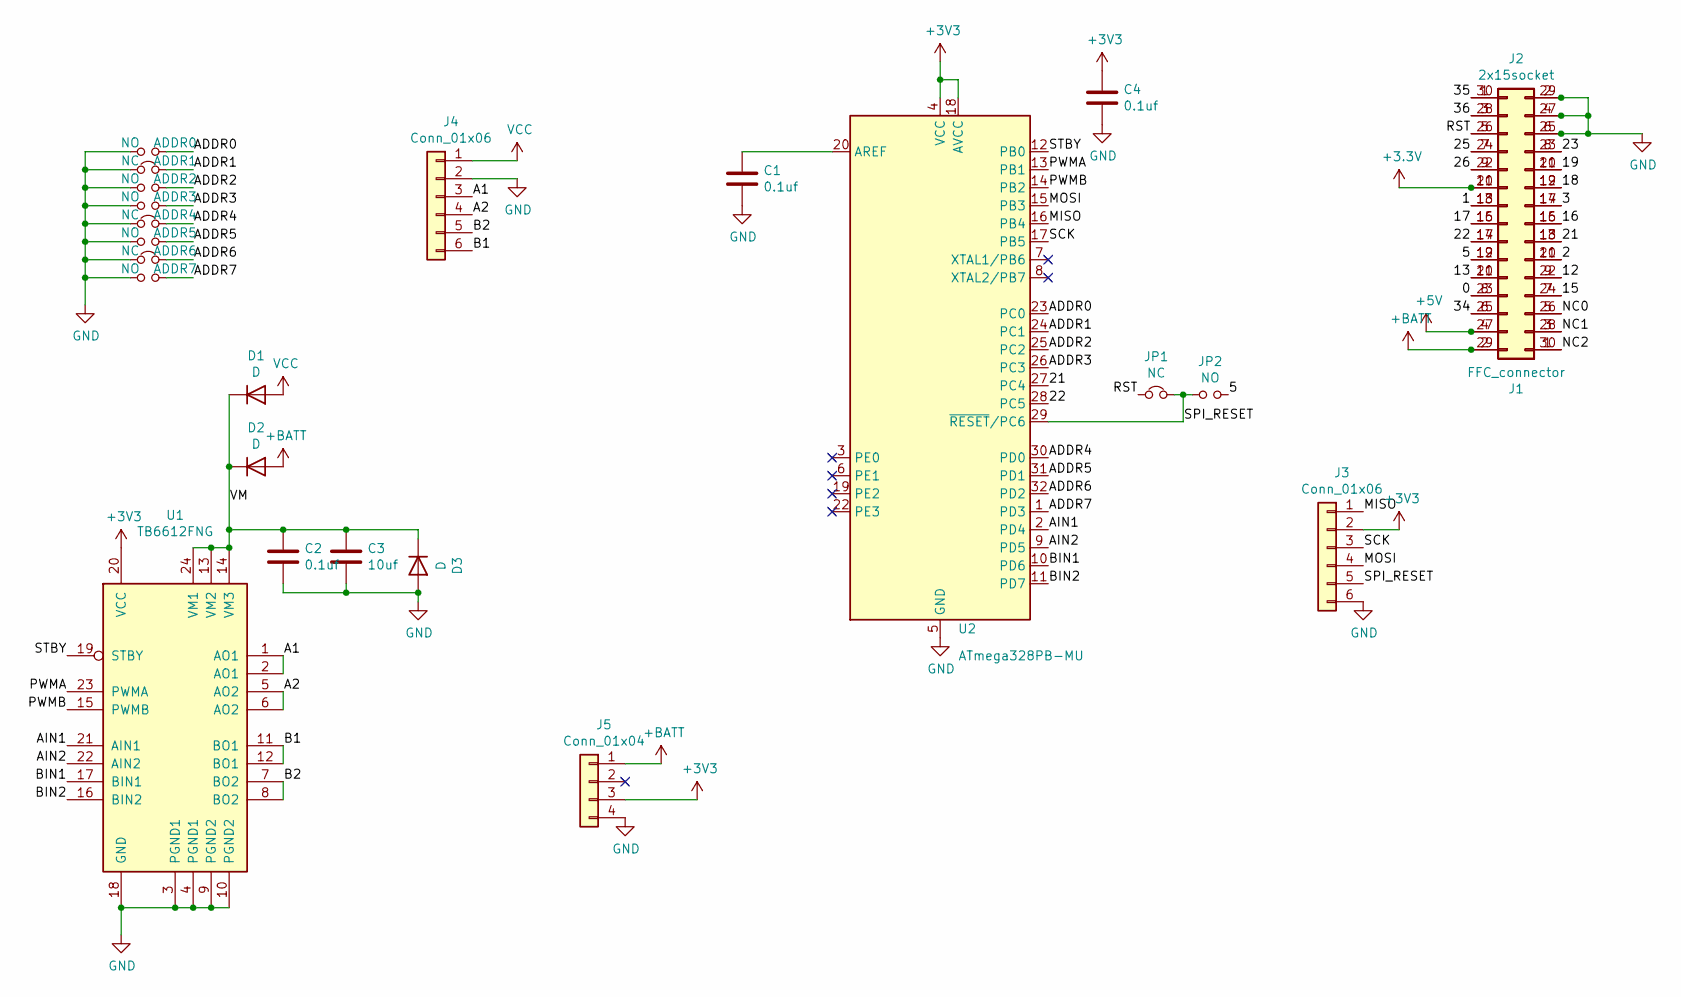
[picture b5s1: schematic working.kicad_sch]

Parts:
ADDR0, ADDR2, ADDR3, ADDR5, ADDR7: NO; SolderJumper-2_P1.3mm_Open_RoundedPad1.0x1.5mm
ADDR1, ADDR4, ADDR6: NC; SolderJumper-2_P1.3mm_Bridged_RoundedPad1.0x1.5mm
C1, C2, C4: 0.1uf; C_0603_1608Metric
C3: 10uf; C_0805_2012Metric
D1, D2, D3: D; D_SOD-123F
J1: FFC_connector; Hirose_FH12-30S-0.5SH_1x30-1MP_P0.50mm_Horizontal
J2: 2x15socket; PinSocket_2x15_P2.54mm_Vertical_SMD_just_for_M5Stack_bottom
J3: Conn_01x06; 2x03_P2.54mm_Pads
J4: Conn_01x06; TerminalBlock_bornier-6_P5.08mm
J5: Conn_01x04; NS-Tech_Grove_1x04_P2mm_Vertical
JP1: NC; SolderJumper-2_P1.3mm_Bridged_RoundedPad1.0x1.5mm
JP2: NO; SolderJumper-2_P1.3mm_Open_RoundedPad1.0x1.5mm
U1: TB6612FNG; SSOP-24_5.3x8.2mm_P0.65mm
U2: ATmega328PB-MU; QFN-32-1EP_5x5mm_P0.5mm_EP3.1x3.1mm

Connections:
+5V: J1.4, J2.27
+BATT: D2.2 (A), J1.2, J2.29, J5.1
/0: J1.8, J2.23
/1: J1.18, J2.13
/2: J1.11, J2.20
/3: J1.17, J2.14
/5: J1.12, J2.19, JP2.2
/12: J1.9, J2.22
/13: J1.10, J2.21
/15: J1.7, J2.24
/16: J1.15, J2.16
/17: J1.16, J2.15
/18: J1.19, J2.12
/19: J1.21, J2.10
/21: J1.13, J2.18, U2.27 (PC4)
/22: J1.14, J2.17, U2.28 (PC5)
/23: J1.23, J2.8
/25: J1.24, J2.7
/26: J1.22, J2.9
/34: J1.6, J2.25
/35: J1.30, J2.1
/36: J1.28, J2.3
/A1: J4.3, U1.1 (AO1), U1.2 (AO1)
/A2: J4.4, U1.5 (AO2), U1.6 (AO2)
/ADDR0: ADDR0.2, U2.23 (PC0)
/ADDR1: ADDR1.2, U2.24 (PC1)
/ADDR2: ADDR2.2, U2.25 (PC2)
/ADDR3: ADDR3.2, U2.26 (PC3)
/ADDR4: ADDR4.2, U2.30 (PD0)
/ADDR5: ADDR5.2, U2.31 (PD1)
/ADDR6: ADDR6.2, U2.32 (PD2)
/ADDR7: ADDR7.2, U2.1 (PD3)
/AIN1: U1.21 (AIN1), U2.2 (PD4)
/AIN2: U1.22 (AIN2), U2.9 (PD5)
/B1: J4.6, U1.11 (BO1), U1.12 (BO1)
/B2: J4.5, U1.7 (BO2), U1.8 (BO2)
/BIN1: U1.17 (BIN1), U2.10 (PD6)
/BIN2: U1.16 (BIN2), U2.11 (PD7)
/MISO: J3.1, U2.16 (PB4)
/MOSI: J3.4, U2.15 (PB3)
/NC0: J1.5, J2.26
/NC1: J1.3, J2.28
/NC2: J1.1, J2.30
/PWMA: U1.23 (PWMA), U2.13 (PB1)
/PWMB: U1.15 (PWMB), U2.14 (PB2)
/RST: J1.26, J2.5, JP1.1
/SCK: J3.3, U2.17 (PB5)
/SPI_RESET: J3.5, JP1.2, JP2.1, U2.29 (~RESET/PC6)
/STBY: U1.19 (STBY), U2.12 (PB0)
/VM: C2.1, C3.1, D1.1 (K), D2.1 (K), D3.1 (K), U1.13 (VM2), U1.14 (VM3), U1.24 (VM1)
GND: ADDR0.1, ADDR1.1, ADDR2.1, ADDR3.1, ADDR4.1, ADDR5.1, ADDR6.1, ADDR7.1, C1.2, C2.2, C3.2, C4.2, D3.2 (A), J1.25, J1.27, J1.29, J2.2, J2.4, J2.6, J3.6, J4.2, J5.4, U1.3 (PGND1), U1.4 (PGND1), U1.9 (PGND2), U1.10 (PGND2), U1.18 (GND), U2.5 (GND), U2.21 (GND), U2.33 (GND)
unnamed: C1.1, U2.20 (AREF)
VCC: D1.2 (A), J4.1

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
